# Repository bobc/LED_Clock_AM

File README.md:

# About LED_Clock_AM
An LED clock with Arduino Mini/Micro

Replica of "Tix(tm)" style LED clock with accurate Maxim Real Time Clock chip (DS3231). Uses an Arduino Micro or Mini (or compatible).

##Copyright

Open Source Hardware, licensed with CERN OHL.

Copyright (c) 2016 Bob Cousins  

This documentation describes Open Hardware and is licensed under the
CERN OHL v. 1.1.  You may redistribute and modify this documentation
under the terms of the CERN OHL v.1.1. (http://ohwr.org/cernohl). This
documentation is distributed WITHOUT ANY EXPRESS OR IMPLIED WARRANTY,
INCLUDING OF MERCHANTABILITY, SATISFACTORY QUALITY AND FITNESS FOR A
PARTICULAR PURPOSE. Please see the CERN OHL v.1.1 for applicable
conditions

You can find a copy of the CERN OHL v.1.1 in the file "LICENSE". Please also read "LICENSE.HOWTO".

##External dependencies

- KiCad 4.0.x, with included symbol libaries and 3D symbols http://kicad-pcb.org/download/
- KiCad footprints (4.0.0 release)  
- RMC libraries
- Walter Lain libraries  http://smisioto.no-ip.org/elettronica/kicad/kicad-en.htm

##Fabrication outputs

Gerbers are in the "gerbers" folder.  
The zip file is for submission to ITeadMall, probably could be used for other fab houses.  
The gvp file is for use with gerbv (http://gerbv.geda-project.org/).

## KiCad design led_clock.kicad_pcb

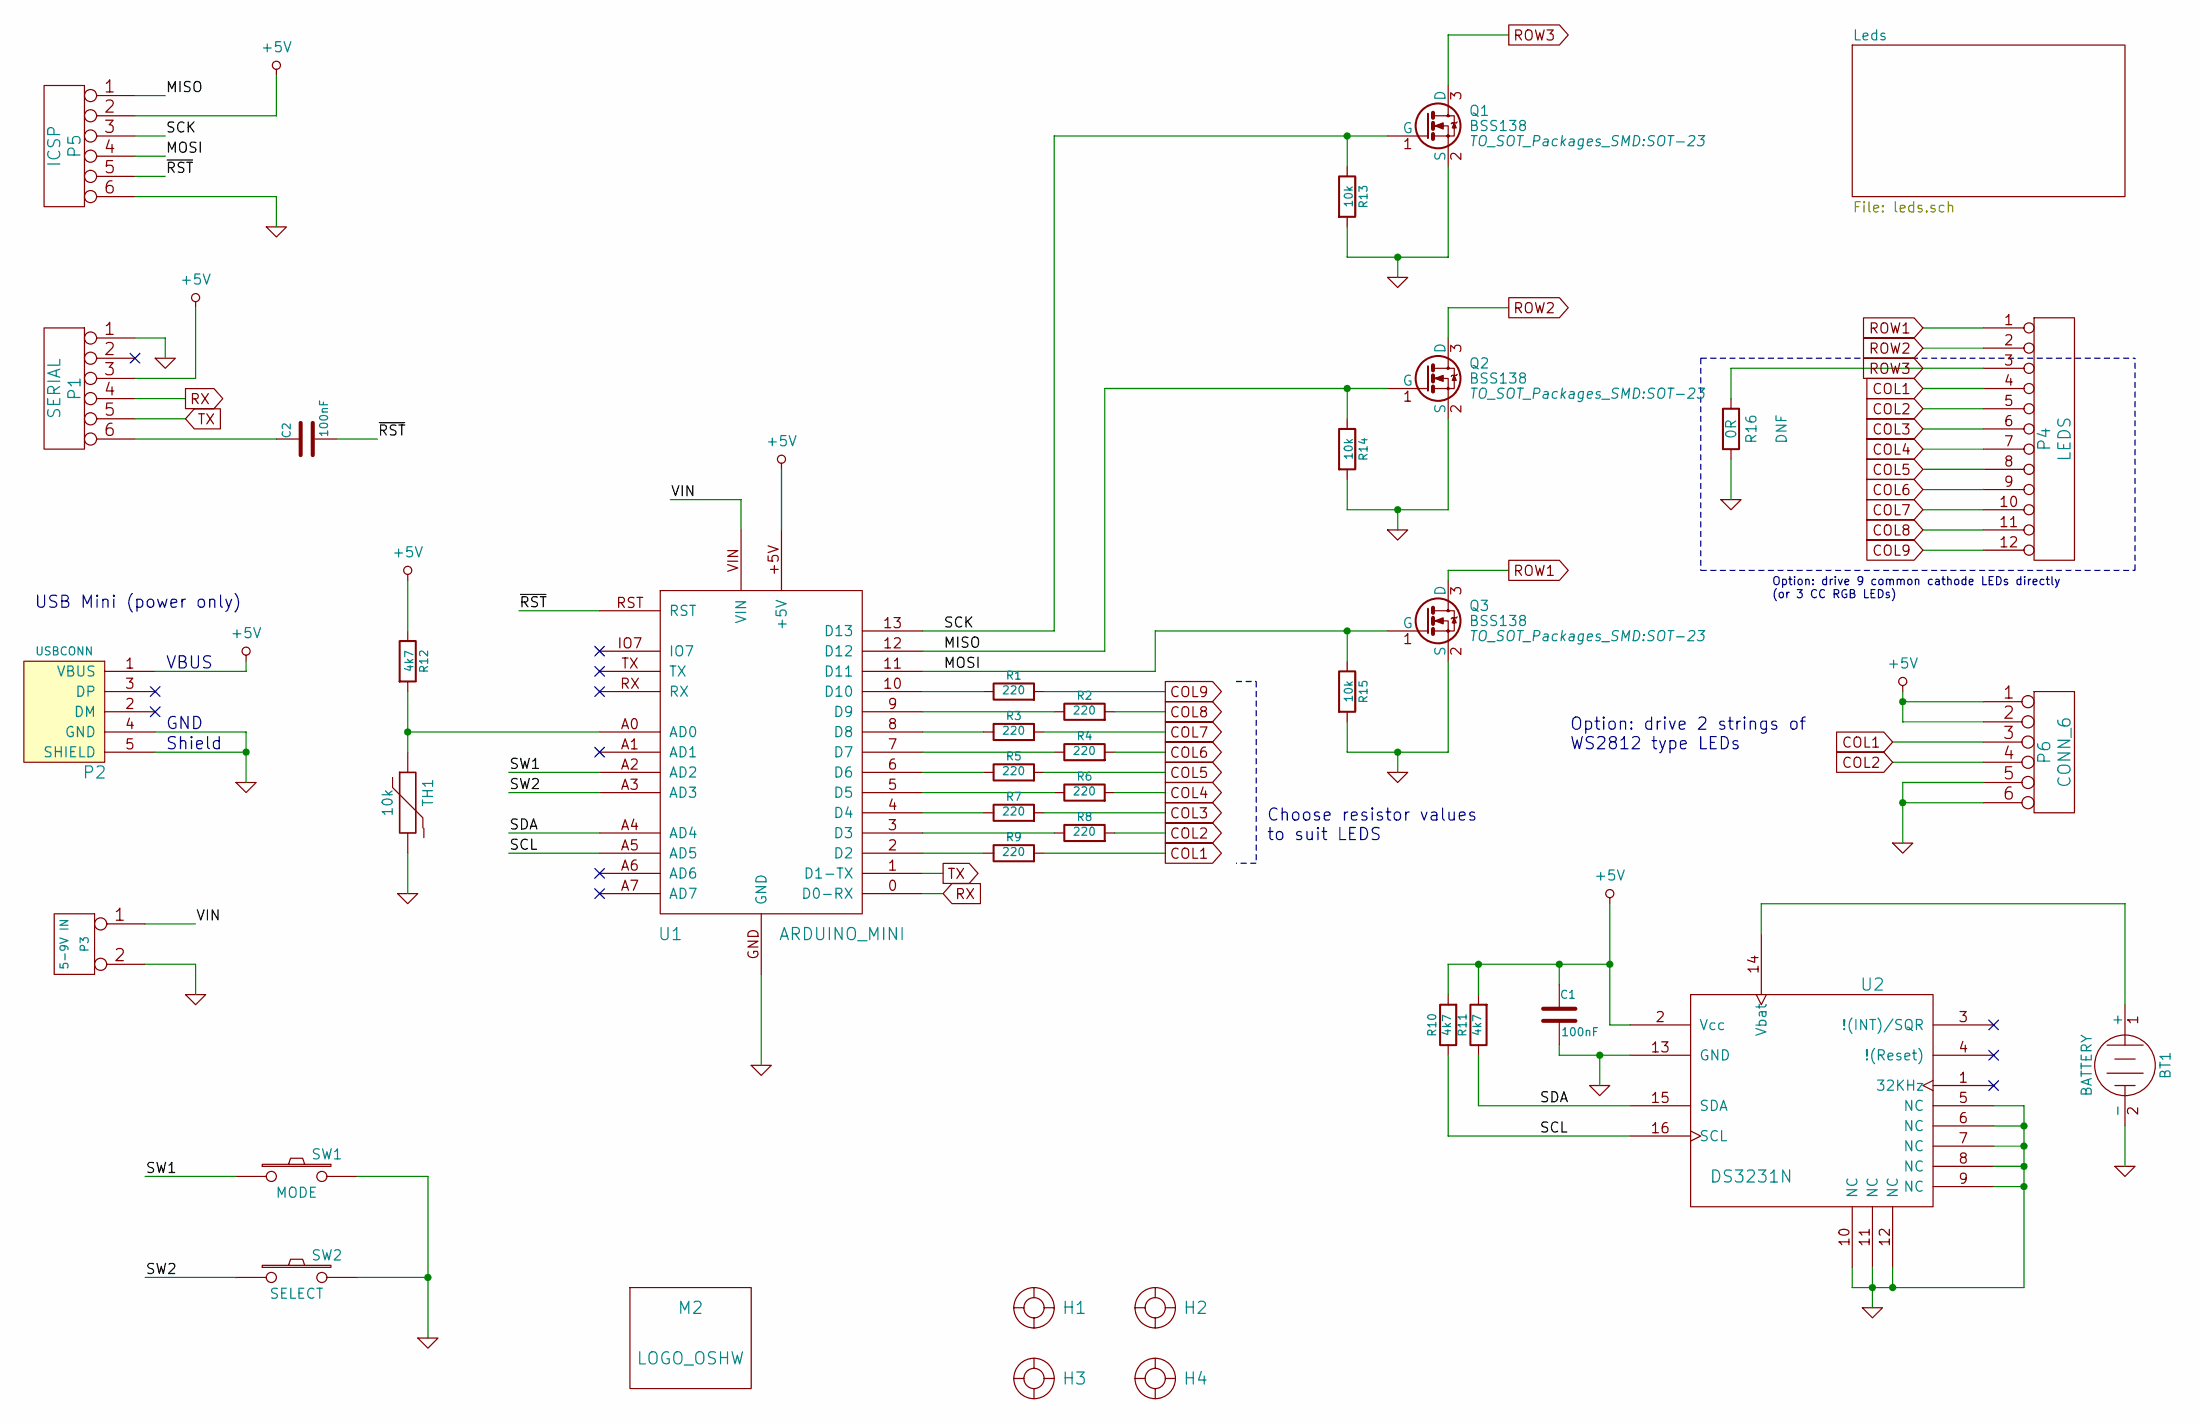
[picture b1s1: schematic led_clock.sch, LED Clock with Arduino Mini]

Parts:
BT1: BATTERY; keystone_106
C1, C2: 100nF; C_0805
H1, H2, H3, H4: HOLE_RMC; HOLE_M3
M2: LOGO_OSHW; OSHW_logo_2
P1: SERIAL; pin_strip_6
P2: USBCONN; CONN_MiniAB_SMT_RMC
P3: 5-9V IN; pin_strip_2
P4: LEDS; PIN_ARRAY_6x2_RMC
P5: ICSP; pin_strip_3x2
P6: CONN_6; Pin_Header_Straight_1x06
Q1, Q2, Q3: BSS138; SOT-23
R1, R2, R3, R4, R5, R6, R7, R8, R9: 220; R_0805
R10, R11, R12: 4k7; R_0805
R13, R14, R15: 10k; R_0805
R16: 0R; R_0805
SW1: MODE; SW_6x6_MULTI
SW2: SELECT; SW_6x6_MULTI
TH1: 10k; R_0805
U1: ARDUINO_MINI
U2: DS3231N; SOIC-16_7.5x10.3mm_Pitch1.27mm

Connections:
+5V: C1.1, P1.3, P2.1 (VBUS), P5.2, P6.1, P6.2, R10.2, R11.2, R12.1, U1.+5V, U2.2 (Vcc)
/MISO: P5.1, Q2.1 (G), R14.1, U1.12 (D12)
/MOSI: P5.4, Q3.1 (G), R15.1, U1.11 (D11)
/SCK: P5.3, Q1.1 (G), R13.1, U1.13 (D13)
/SCL: R10.1, U1.A5 (AD5), U2.16 (SCL)
/SDA: R11.1, U1.A4 (AD4), U2.15 (SDA)
/SW1: SW1.1, U1.A2 (AD2)
/SW2: SW2.1, U1.A3 (AD3)
/VIN: P3.1, U1.VIN
/~RST: C2.2, P5.5, U1.RST
COL1: P4.4, P6.3, R9.2; also elsewhere on the board
COL2: P4.5, P6.4, R8.2; also elsewhere on the board
COL3: P4.6, R7.2; also elsewhere on the board
COL4: P4.7, R6.2; also elsewhere on the board
COL5: P4.8, R5.2; also elsewhere on the board
COL6: P4.9, R4.2; also elsewhere on the board
COL7: P4.10, R3.2; also elsewhere on the board
COL8: P4.11, R2.2; also elsewhere on the board
COL9: P4.12, R1.2; also elsewhere on the board
GND: BT1.2 (-), C1.2, P1.1, P2.4 (GND), P2.5 (SHIELD), P3.2 (PM), P5.6, P6.5, P6.6, Q1.2 (S), Q2.2 (S), Q3.2 (S), R13.2, R14.2, R15.2, R16.2, SW1.2, SW2.2, TH1.2, U1.GND, U2.5 (NC), U2.6 (NC), U2.7 (NC), U2.8 (NC), U2.9 (NC), U2.10 (NC), U2.11 (NC), U2.12 (NC), U2.13 (GND)
unnamed: BT1.1 (+), U2.14 (Vbat)
unnamed: C2.1, P1.6
unnamed: R1.1, U1.10 (D10)
unnamed: R2.1, U1.9 (D9)
unnamed: R3.1, U1.8 (D8)
unnamed: R4.1, U1.7 (D7)
unnamed: R5.1, U1.6 (D6)
unnamed: R6.1, U1.5 (D5)
unnamed: R7.1, U1.4 (D4)
unnamed: R8.1, U1.3 (D3)
unnamed: R9.1, U1.2 (D2)
unnamed: R12.2, TH1.1, U1.A0 (AD0)
ROW1: P4.1, Q3.3 (D); also elsewhere on the board
ROW2: P4.2, Q2.3 (D); also elsewhere on the board
ROW3: P4.3, Q1.3 (D), R16.1; also elsewhere on the board
RX: P1.4, U1.0 (D0-RX)
TX: P1.5, U1.1 (D1-TX)

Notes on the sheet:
USB Mini (power only)
GND
Shield
VBUS
Option: drive 9 common cathode LEDs directly (or 3 CC RGB LEDs)
Option: drive 2 strings of WS2812 type LEDs
Choose resistor values to suit LEDS

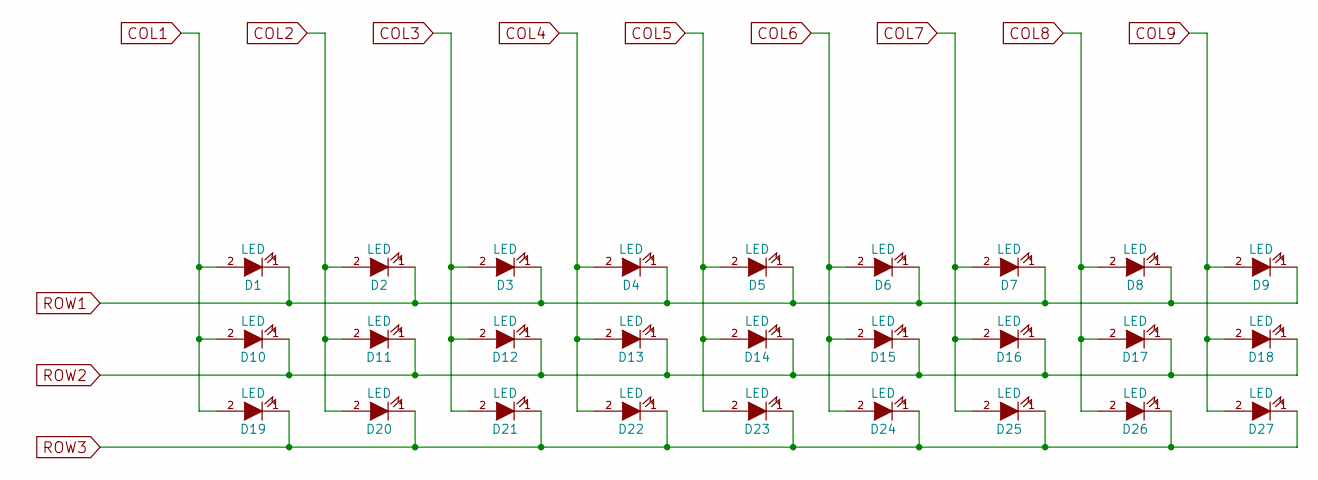
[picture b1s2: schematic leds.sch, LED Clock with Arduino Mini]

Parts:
D1, D7, D8, D9, D10, D16, D17, D18, D19, D25, D26, D27: LED; LED-0805_RED
D2, D3, D4, D11, D12, D13, D20, D21, D22: LED; LED-0805_GREEN
D5, D6, D14, D15, D23, D24: LED; LED-0805_BLUE

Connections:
COL1: D1.2 (A), D10.2 (A), D19.2 (A); also elsewhere on the board
COL2: D2.2 (A), D11.2 (A), D20.2 (A); also elsewhere on the board
COL3: D3.2 (A), D12.2 (A), D21.2 (A); also elsewhere on the board
COL4: D4.2 (A), D13.2 (A), D22.2 (A); also elsewhere on the board
COL5: D5.2 (A), D14.2 (A), D23.2 (A); also elsewhere on the board
COL6: D6.2 (A), D15.2 (A), D24.2 (A); also elsewhere on the board
COL7: D7.2 (A), D16.2 (A), D25.2 (A); also elsewhere on the board
COL8: D8.2 (A), D17.2 (A), D26.2 (A); also elsewhere on the board
COL9: D9.2 (A), D18.2 (A), D27.2 (A); also elsewhere on the board
ROW1: D1.1 (K), D2.1 (K), D3.1 (K), D4.1 (K), D5.1 (K), D6.1 (K), D7.1 (K), D8.1 (K), D9.1 (K); also elsewhere on the board
ROW2: D10.1 (K), D11.1 (K), D12.1 (K), D13.1 (K), D14.1 (K), D15.1 (K), D16.1 (K), D17.1 (K), D18.1 (K); also elsewhere on the board
ROW3: D19.1 (K), D20.1 (K), D21.1 (K), D22.1 (K), D23.1 (K), D24.1 (K), D25.1 (K), D26.1 (K), D27.1 (K); also elsewhere on the board

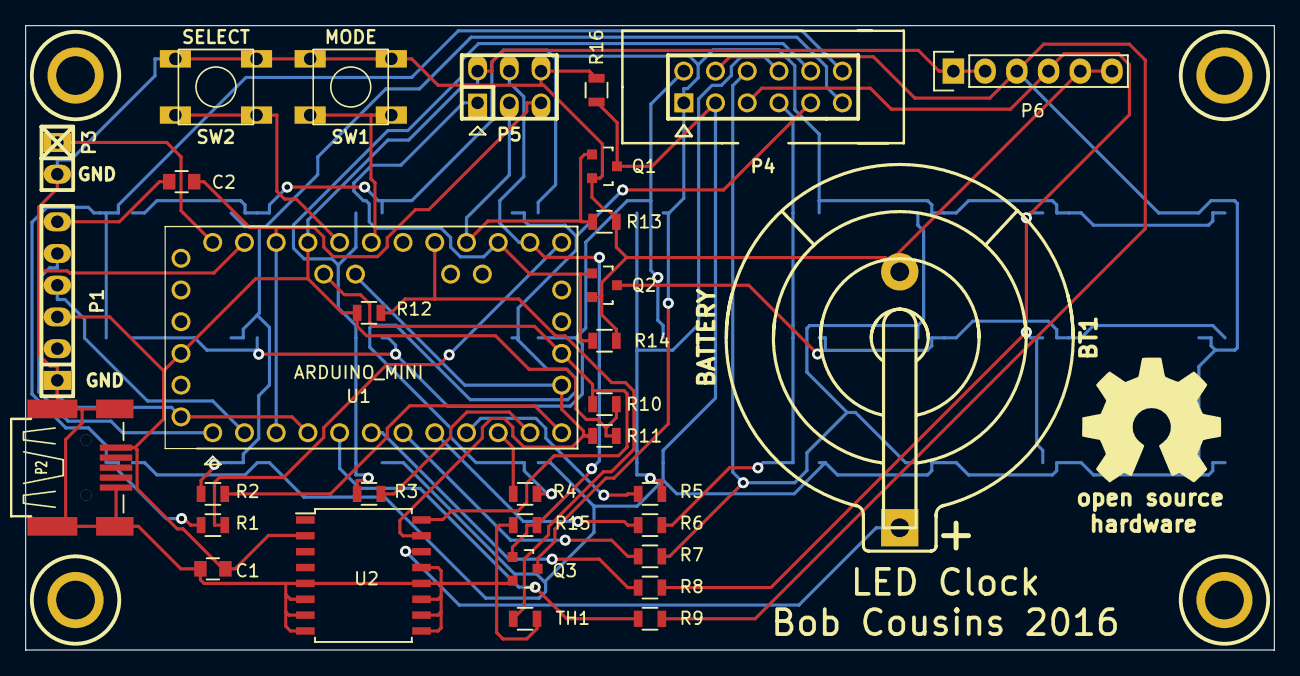
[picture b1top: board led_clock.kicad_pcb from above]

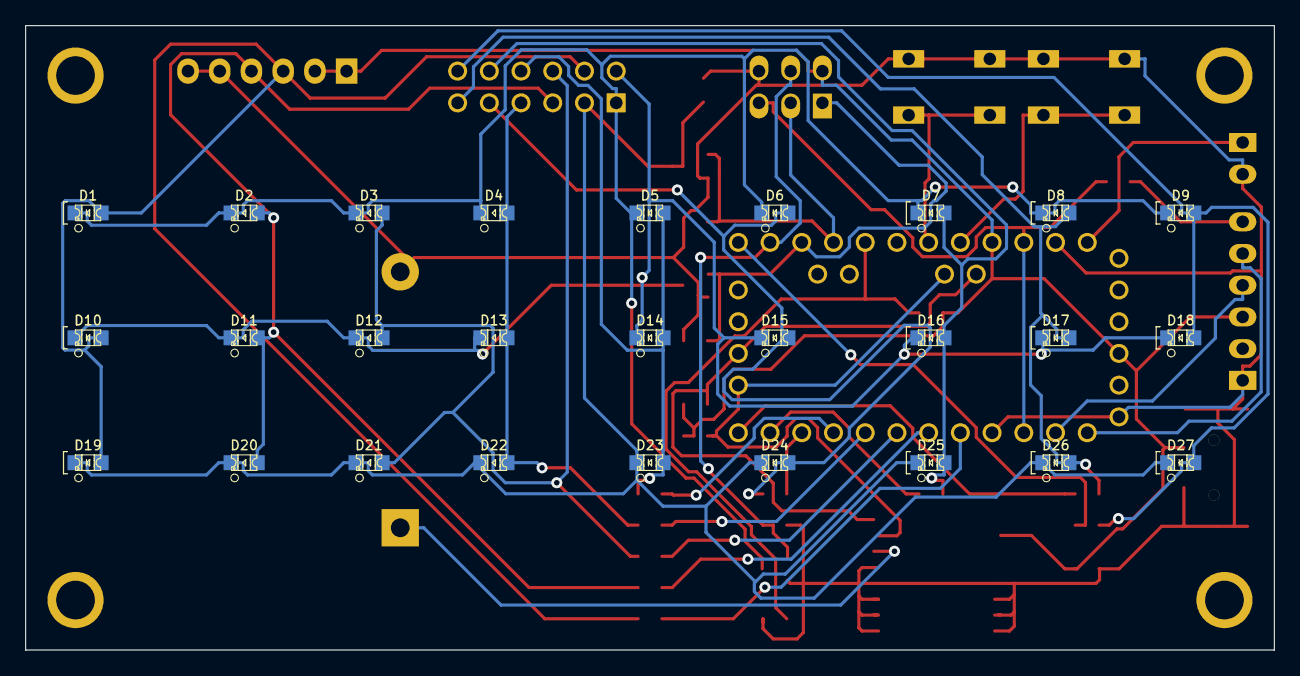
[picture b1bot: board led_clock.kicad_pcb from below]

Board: 2 copper layers, 100.0 x 50.0 mm, 65 parts (27 on the bottom side), 37 nets.

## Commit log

2016-02-20 Version 1
2016-02-20 Update gitignore
2016-02-20 Added some docs
2016-02-20 Update logo
2016-02-20 Update license info.
2016-02-21 Remove old gerbers
2016-02-21 New gerbers; fix problem with USB connector not connected to GND
2016-02-21 Remove unneeded lib; update to new pretty format libs
2016-02-21 Remove references to unused libs/symbols
2016-02-21 Fix up paths for 3D models
2016-02-21 Add sketch for Arduino
